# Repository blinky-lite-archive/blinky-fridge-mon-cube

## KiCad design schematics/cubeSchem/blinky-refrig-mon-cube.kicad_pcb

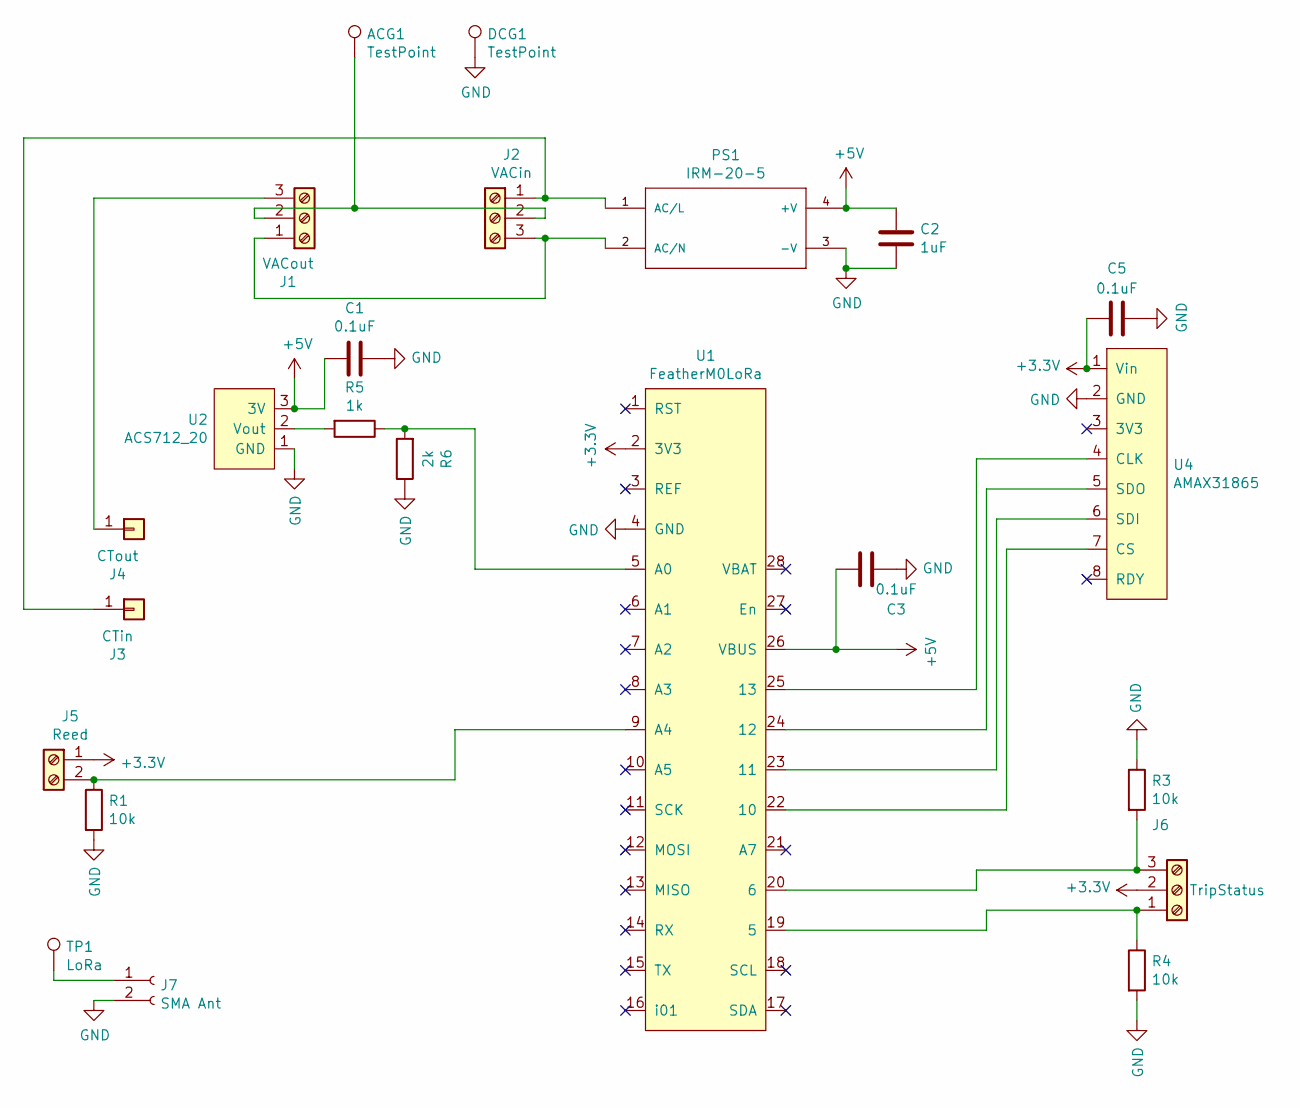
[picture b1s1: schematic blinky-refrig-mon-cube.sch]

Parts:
ACG1: TestPoint; TestPoint_THTPad_3.0x3.0mm_Drill1.5mm
C1, C3, C5: 0.1uF; C_1206_3216Metric_Pad1.42x1.75mm_HandSolder
C2: 1uF; C_1206_3216Metric_Pad1.42x1.75mm_HandSolder
DCG1: TestPoint; TestPoint_THTPad_3.0x3.0mm_Drill1.5mm
J1: VACout; TerminalBlock_bornier-3_P5.08mm
J2: VACin; TerminalBlock_bornier-3_P5.08mm
J3: CTin; SolderWirePad_1x01_Drill1.5mm
J4: CTout; SolderWirePad_1x01_Drill1.5mm
J5: Reed; TerminalBlock_bornier-2_P5.08mm
J6: TripStatus; TerminalBlock_bornier-3_P5.08mm
J7: SMA Ant; SMA_pcb
PS1: IRM-20-5; CONV_IRM-20-5
R1, R3, R4: 10k; R_1206_3216Metric_Pad1.42x1.75mm_HandSolder
R5: 1k; R_1206_3216Metric_Pad1.42x1.75mm_HandSolder
R6: 2k; R_1206_3216Metric_Pad1.42x1.75mm_HandSolder
TP1: LoRa; TestPoint_Plated_Hole_D2.0mm
U1: FeatherM0LoRa
U2: ACS712_20; ACS712_20A
U4: AMAX31865

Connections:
+3V3: C5.2, J5.1, J6.2, U1.2 (3V3), U4.1 (Vin)
+5V: C1.2, C2.1, C3.2, PS1.4 (+V), U1.26 (VBUS), U2.3 (3V)
GND: C1.1, C2.2, C3.1, C5.1, DCG1.1, J7.2, PS1.3 (-V), R1.2, R3.1, R4.2, R6.1, U1.4 (GND), U2.1 (GND), U4.2 (GND)
unnamed: ACG1.1, J1.2, J2.2
unnamed: J1.1, J2.3, PS1.2 (AC/N)
unnamed: J1.3, J4.1
unnamed: J2.1, J3.1, PS1.1 (AC/L)
unnamed: J5.2, R1.1, U1.9 (A4)
unnamed: J6.1, R4.1, U1.19 (5)
unnamed: J6.3, R3.2, U1.20 (6)
unnamed: J7.1, TP1.1
unnamed: R5.1, R6.2, U1.5 (A0)
unnamed: R5.2, U2.2 (Vout)
unnamed: U1.22 (10), U4.7 (CS)
unnamed: U1.23 (11), U4.6 (SDI)
unnamed: U1.24 (12), U4.5 (SDO)
unnamed: U1.25 (13), U4.4 (CLK)

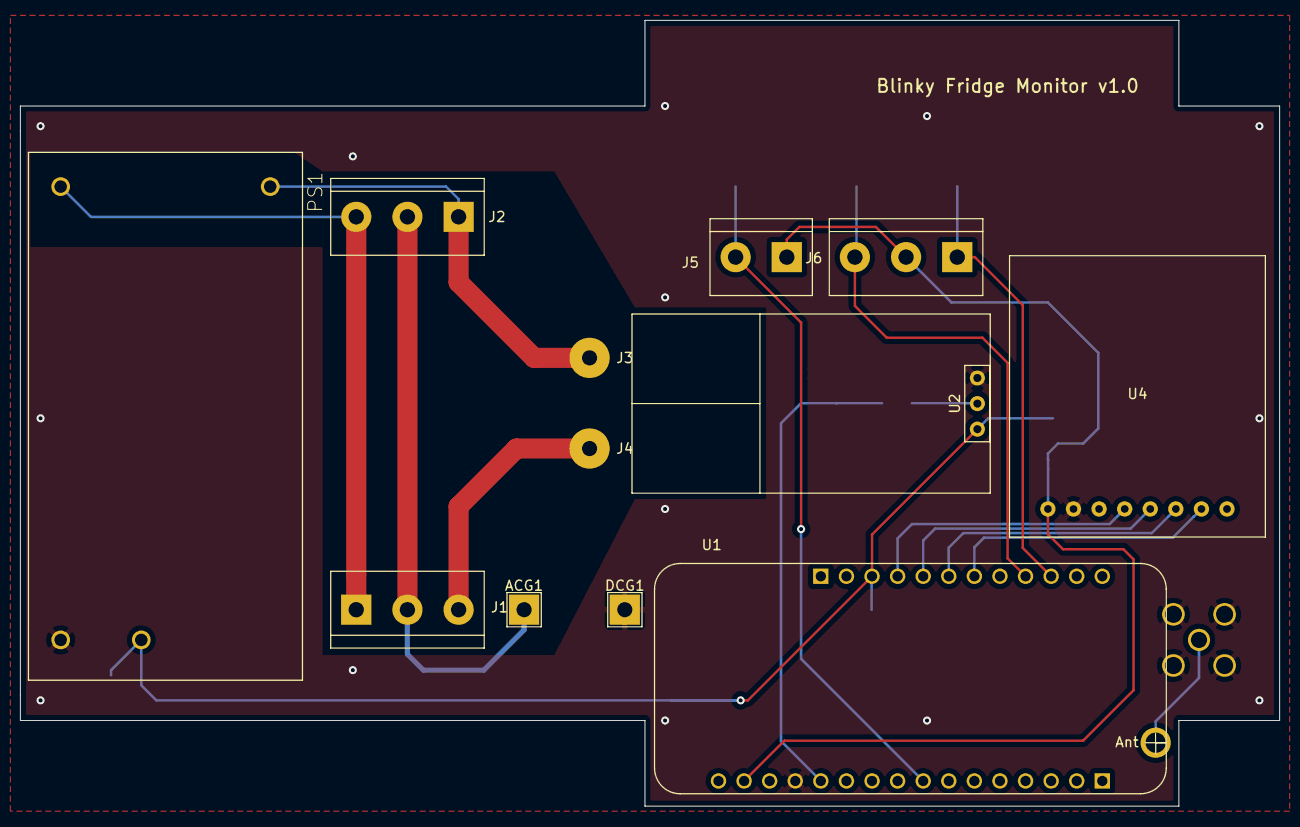
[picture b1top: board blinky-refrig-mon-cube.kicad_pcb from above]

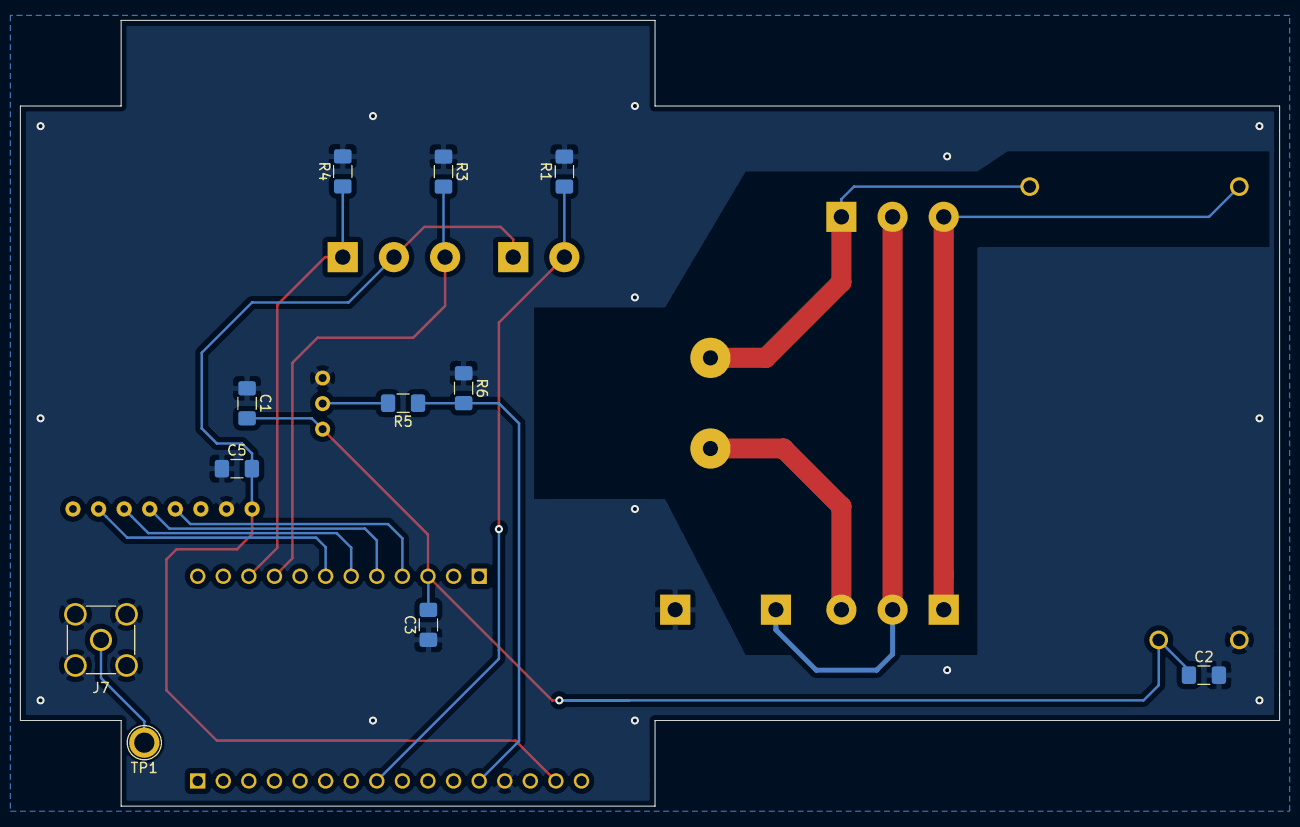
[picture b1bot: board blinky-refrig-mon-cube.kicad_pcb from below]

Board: 2 copper layers, 125.0 x 78.0 mm, 23 parts (11 on the bottom side), 17 nets.

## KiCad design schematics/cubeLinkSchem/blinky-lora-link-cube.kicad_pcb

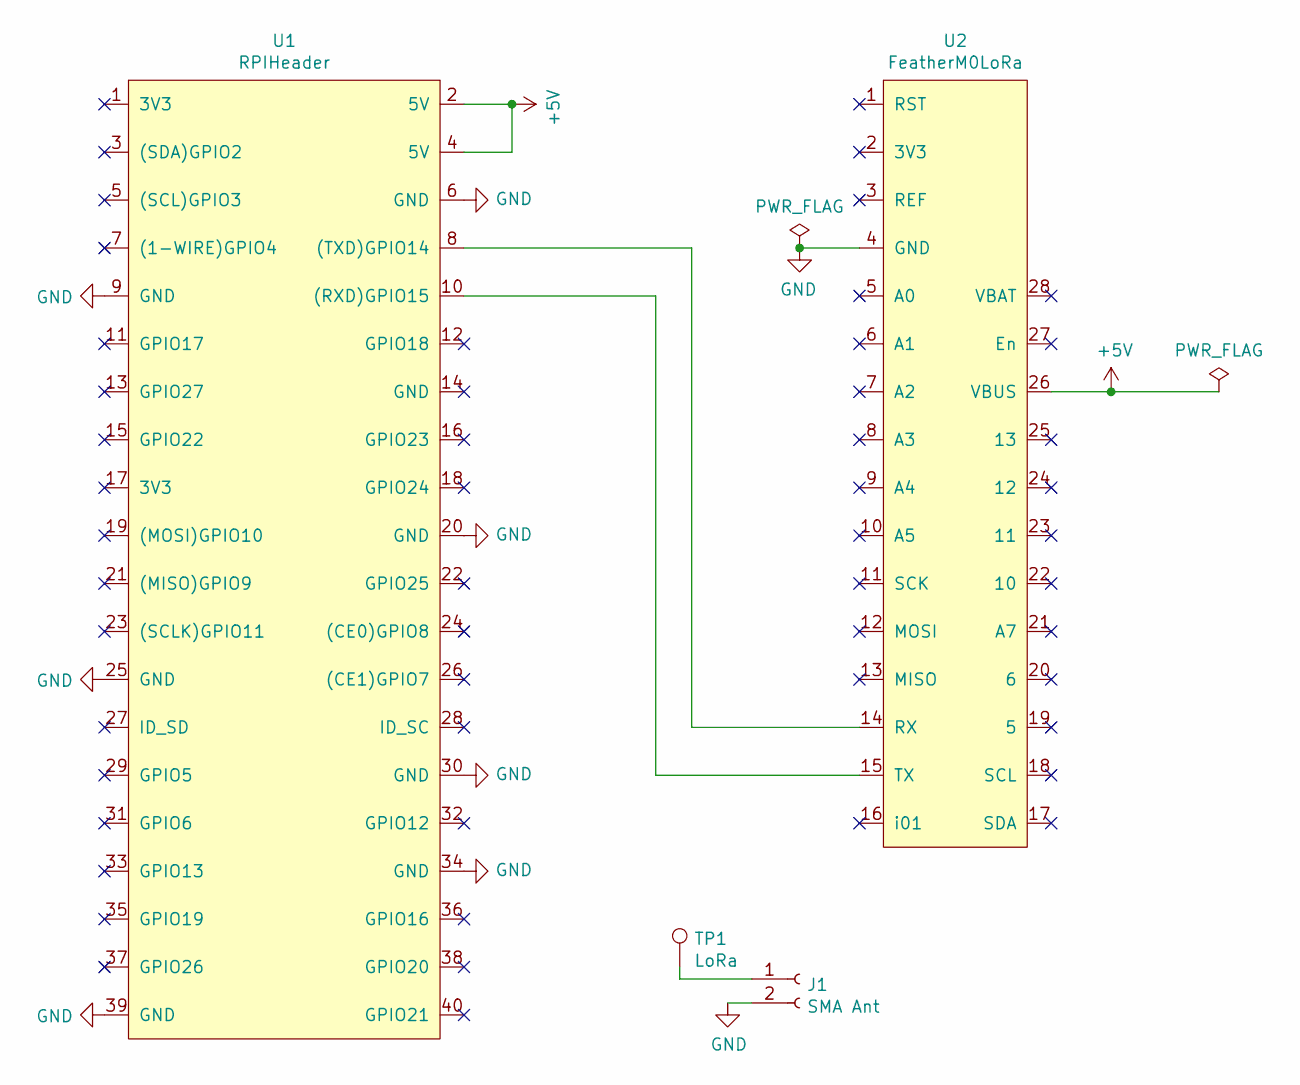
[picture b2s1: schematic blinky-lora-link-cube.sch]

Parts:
J1: SMA Ant; SMA_pcb
TP1: LoRa; TestPoint_Plated_Hole_D2.0mm
U1: RPIHeader; PinHeader_2x20_P2.54mm_Vertical
U2: FeatherM0LoRa

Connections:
+5V: U1.2 (5V), U1.4 (5V), U2.26 (VBUS)
GND: J1.2, U1.6 (GND), U1.9 (GND), U1.20 (GND), U1.25 (GND), U1.30 (GND), U1.34 (GND), U1.39 (GND), U2.4 (GND)
unnamed: J1.1, TP1.1
unnamed: U1.8 ((TXD)GPIO14), U2.14 (RX)
unnamed: U1.10 ((RXD)GPIO15), U2.15 (TX)

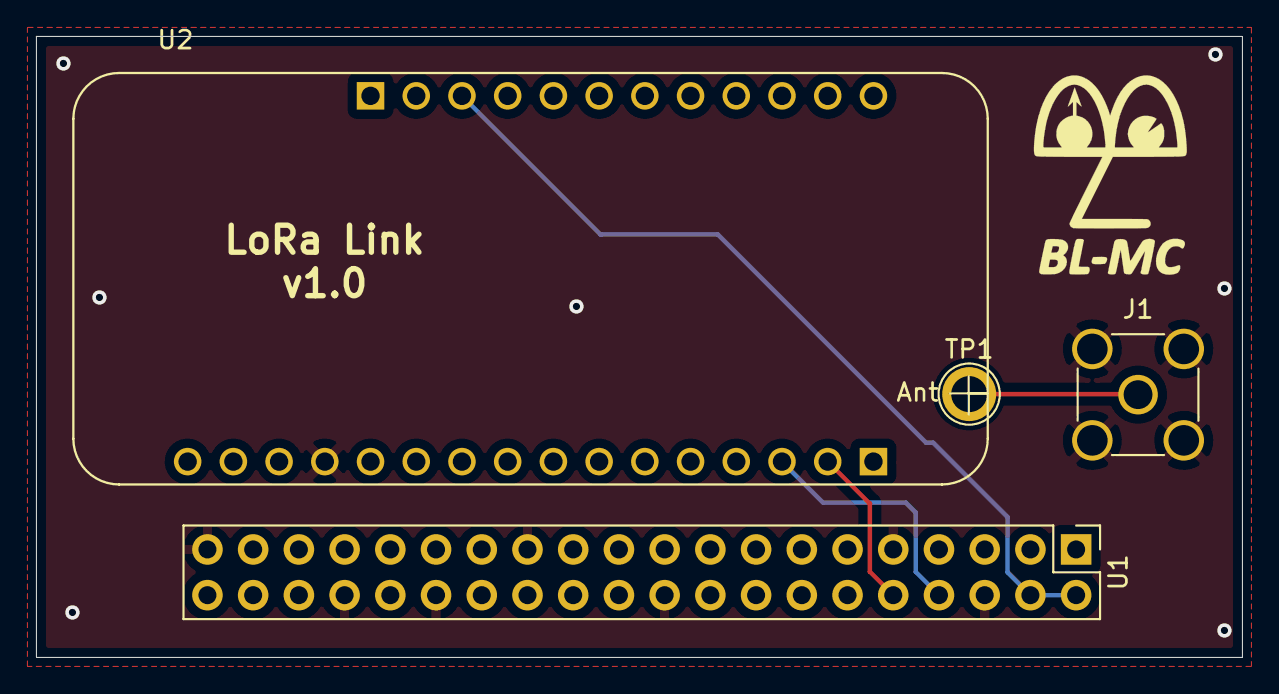
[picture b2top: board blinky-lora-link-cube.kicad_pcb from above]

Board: 2 copper layers, 67.0 x 34.5 mm, 4 parts (0 on the bottom side), 5 nets.

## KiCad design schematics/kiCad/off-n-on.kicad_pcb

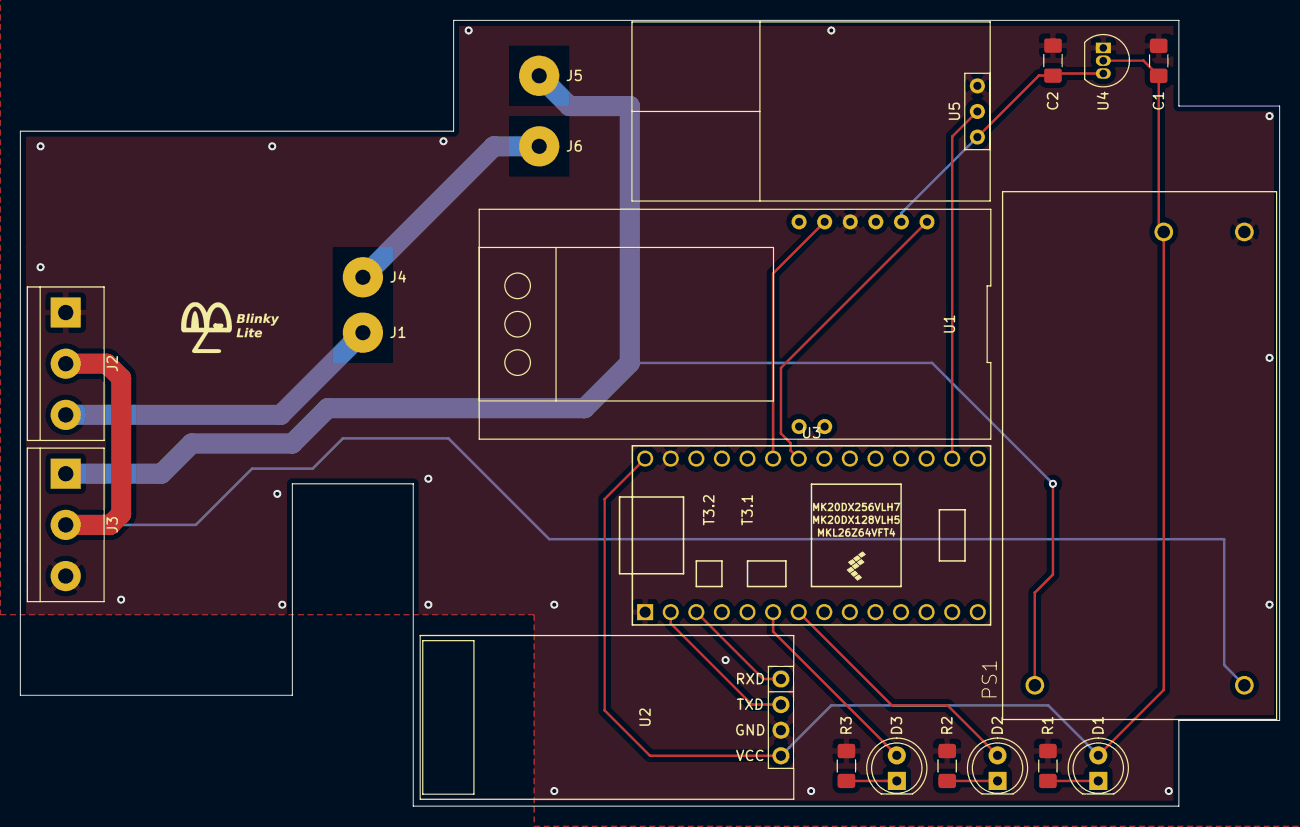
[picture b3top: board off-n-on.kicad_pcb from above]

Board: 2 copper layers, 125.0 x 78.0 mm, 20 parts (0 on the bottom side), 17 nets.

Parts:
C1, C2: 1uF; C_1206_3216Metric_Pad1.42x1.75mm_HandSolder
D1: GREEN; LED_D5.0mm
D2: BLUE; LED_D5.0mm
D3: RED; LED_D5.0mm
J1: PFno; SolderWirePad_1x01_Drill1.5mm
J2: VACout; TerminalBlock_bornier-3_P5.08mm
J3: VACin; TerminalBlock_bornier-3_P5.08mm
J4: PFcom; SolderWirePad_1x01_Drill1.5mm
J5: CTin; SolderWirePad_1x01_Drill1.5mm
J6: CTout; SolderWirePad_1x01_Drill1.5mm
PS1: IRM-20-5; CONV_IRM-20-5
R1, R2, R3: 220; R_1206_3216Metric_Pad1.42x1.75mm_HandSolder
U1: PowerFeather
U2: HC06
U3: Teensy-LC; Teensy30_31_32_LC
U4: MCP1700-3002E_TO92; TO-92_Inline
U5: ACS712_20; ACS712_20A

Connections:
+3V3: C2.1, U1.2, U4.3, U5.3
+5V: C1.1, D1.2, PS1.4, U2.4, U3.33, U4.2
GND: C1.2, C2.2, J2.1, J3.3, PS1.3, R1.2, R2.2, R3.2, U1.4, U2.3, U3.1, U3.32, U4.1, U5.1
unnamed: D1.1, R1.1
unnamed: D2.1, R2.1
unnamed: D2.2, U3.7
unnamed: D3.1, R3.1
unnamed: D3.2, U3.6
unnamed: J1.1, J2.3
unnamed: J2.2, J3.2, PS1.2
unnamed: J3.1, J5.1, PS1.1
unnamed: J4.1, J6.1
unnamed: U1.1, U3.27
unnamed: U1.5, U3.28
unnamed: U2.1, U3.3
unnamed: U2.2, U3.2
unnamed: U3.21, U5.2

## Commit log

2020-03-22 updated schematic
2020-03-24 cube code working with tray
2020-04-01 changed hc06 setup
2020-04-01 added soft 50Hz LPF
2021-09-20 mon and link layout done
2021-09-25 added logo
2021-10-15 added cubelink code
2021-10-17 put delay in modbus poll
2021-10-18 changed link to serila instead of serial1
2021-10-19 added 102
2021-12-13 8 device generic link cube
2021-12-13 cahnged to 125khz lora
2021-12-23 new modbus scheme
2021-12-30 updating power-mon-schem
2022-01-04 laying out pcb for temp mon
2022-01-04 pcb design seems finished
2022-01-04 updated cube code for current meas
2022-01-04 renamed schem files
2022-01-05 fixed lora footprint
